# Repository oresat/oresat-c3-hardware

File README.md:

# oresat-c3
## General information
This is the C3 (Command, Communication, and Control) card for OreSat. It acts as the central control point for the entire OreSat project, provides
telemetry to the ground, and receiver commands. It's the "on board computer" (OBC) of the OreSat bus. It has:

- Octavo OSD335x-SM SIP AM335X-based Cortex A8 Microporcessor
- On Semi AX5043-based L Band (1.265 GHz) receiver
- On Semi AX5043-based UHF Band (436.5 MHz) receiver and transmitter with 1W PA.
- Custom radiation tolerant watchdog timer based on the TI TLV1042 comparator.
- 16 GB eMMC flash data storage
- 1 Mbit of FRAM for high reliability state and variable storage
- Supercapacitor-backed up RTC
- Two antenna deployment circuits
- OreSat Power Domain (OPD) control circuitry

Design materials are on Google docs; we'll post links / PDFs soon.

Bill of Materials (BOM) can be found [here](https://docs.google.com/spreadsheets/d/11vG1kWyrAjmbF5QJM-EhXmvQoF6O47japwYlHF802do/edit#gid=1239769296).

## OreSat C3 version 6 (KiCAD)

Fixes for the radio receivers, version 2 backplane pinout, and lots of little tweaks
after our lessons learned on OreSat0. OH, and a COMPLETE REFACTOR since we switched from
the STM32F439 to an Octavo OSD335x-SM and switched from EAGLE to KICAD. Yikes.

### V6 Software

The C3 runs Python code that interacts with the radios, peripherals, and CAN bus. [Here's more information](https://github.com/oresat/oresat-c3-software).

## OreSat C3 version 5 (EAGLE)

C3 V5 flew on Oresat0, Oregon's first satellite! Everything worked great, except for the
radio receivers (L band LNA oscillated, and UHF LNA was turned off in firmware).

### v5 Firmware

The firmware for the C3 card is written in C and runs on top of ChibiOS, a small RTOS.
It is integrated into the [oresat-firmware](https://github.com/oresat/oresat-firmware) repository.
The firmware application for this project is located
[here](https://github.com/oresat/oresat-firmware/tree/c3_capstone/src/f4/app_c3_v1).

## OreSat C3 version 4 (EAGLE)

C3 V4 is our latest version of the C3 card; it's getting ready for flight in 
Q2 2021 in OreSat0. It's got all of the functionality necessary for flight.

## OreSat C3 V3 (2019-2020 ECE Capstone)

The 2018-2019 ECE Capstone brought the card to version 3. It implements an
STM32F446VET6 IC, the full L band receiver with ultistage LNA, and a UHF radio 
with LNA but no PA for transmitting.

## Breadboard Prototype

Most embedded project starts out as a bunch of development boards strung together;
the C3 is no different! The breadboard prototype for the C3 card implements an
STM32F446RE development board connected to two SPI radios, the OreSat
FlatSat backplane via a CAN transceiver and I2C for the OPD interface,
and a SDIO and SPI connected SD/MMC Card. The breadboard implements
stronger pullups for the I2C lines than the GPIO of the STM32 can
provide. It is currently capable of interfacing with and activating the
OPD connected boards.

## License

All materials in this repo are copyright Portland State Aerospace Society and are licensed under the CERN Open Hardware Licence Version 2 -
Strongly Reciprocal (CERN-OHL-S v2), or any later version. A copy of the license is located in [here](LICENSE.md).

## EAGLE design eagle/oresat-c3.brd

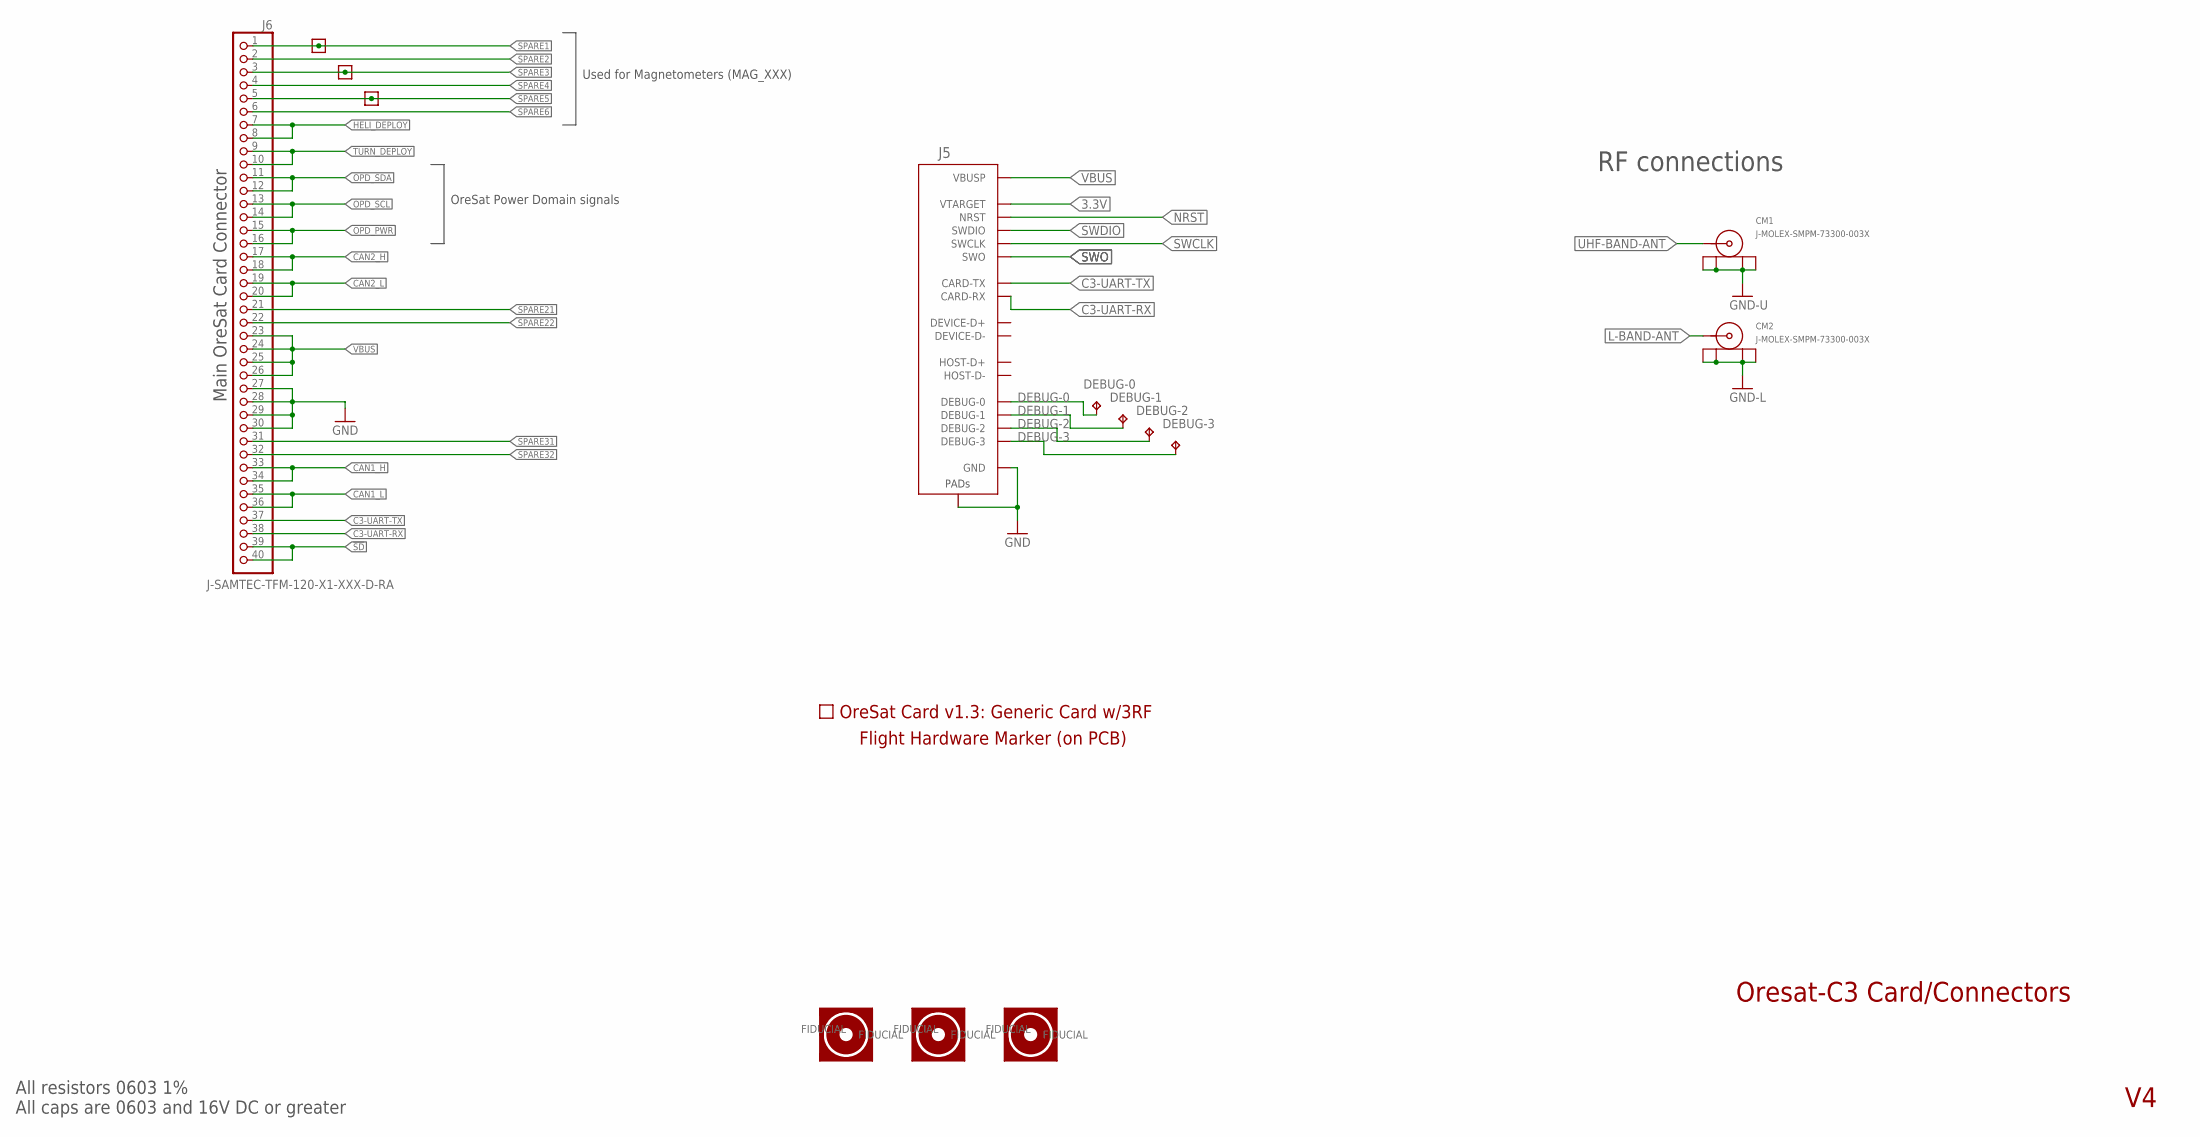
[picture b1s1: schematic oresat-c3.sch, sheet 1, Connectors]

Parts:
CM1, CM2: J-MOLEX-SMPM-73300-003X; J-MOLEX-SMPM-073300-003X; MPN 73300-0020
DEBUG-0, DEBUG-1, DEBUG-2, DEBUG-3: TEST-POINT-SMALL
FIDUCIAL1, FIDUCIAL2, FIDUCIAL3: FIDUCIAL-1.0X2.0
J5: ORESAT-DEBUG-CONNECTOR-ALL; TE_2-1734592-0; MANUFACTURER_PART_NUMBER 2-1734592-0; DIGI-KEY_PART_NUMBER A100287CT-ND
J6: J-SAMTEC-TFM-120-X1-XXX-D-RA; MANUFACTURER_PART_NUMBER TFM-120-01-L-D-RA; DIGI-KEY_PART_NUMBER SAM10145-ND
PCB1: ORESAT-CARD-V1.3-GENERIC-3RF
SPARE3, SPARE4, SPARE5: TEST-POINT-LARGE-SQUARE; 1X01
U$1: FLIGHMARKERNEW; FLIGHTMARKER_NEW_BOARDS

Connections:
3.3V: J5.11 (VTARGET); also elsewhere on the board
!SD: J6.39, J6.40; also elsewhere on the board
C3-UART-RX: J5.12 (CARD-RX), J6.38; also elsewhere on the board
C3-UART-TX: J5.13 (CARD-TX), J6.37; also elsewhere on the board
CAN1_H: J6.33, J6.34; also elsewhere on the board
CAN1_L: J6.35, J6.36; also elsewhere on the board
CAN2_H: J6.17, J6.18; also elsewhere on the board
CAN2_L: J6.19, J6.20; also elsewhere on the board
DEBUG-0: DEBUG-0.TP, J5.17 (DEBUG-0)
DEBUG-1: DEBUG-1.TP, J5.18 (DEBUG-1)
DEBUG-2: DEBUG-2.TP, J5.19 (DEBUG-2)
DEBUG-3: DEBUG-3.TP, J5.20 (DEBUG-3)
GND: J5.3 (GND), J5.6 (GND), J5.9 (GND), J5.PAD1 (PAD), J5.PAD2 (PAD), J6.27, J6.28, J6.29, J6.30; also elsewhere on the board
GND-L: CM2.P$1 (SHIELD3), CM2.P$2 (SHIELD2), CM2.P$3 (SHIELD1), CM2.P$4 (SHIELD); also elsewhere on the board
GND-U: CM1.P$1 (SHIELD3), CM1.P$2 (SHIELD2), CM1.P$3 (SHIELD1), CM1.P$4 (SHIELD); also elsewhere on the board
HELI_DEPLOY: J6.7, J6.8; also elsewhere on the board
L-BAND-ANT: CM2.RF (CENTER); also elsewhere on the board
NRST: J5.10 (NRST); also elsewhere on the board
OPD_PWR: J6.15, J6.16; also elsewhere on the board
OPD_SCL: J6.13, J6.14; also elsewhere on the board
OPD_SDA: J6.11, J6.12; also elsewhere on the board
SPARE1: J6.1, SPARE5.1
SPARE2: J6.2
SPARE3: J6.3, SPARE4.1
SPARE4: J6.4
SPARE5: J6.5, SPARE3.1
SPARE6: J6.6
SPARE21: J6.21
SPARE22: J6.22
SPARE31: J6.31
SPARE32: J6.32
SWCLK: J5.15 (SWCLK); also elsewhere on the board
SWDIO: J5.14 (SWDIO); also elsewhere on the board
SWO: J5.16 (SWO); also elsewhere on the board
TURN_DEPLOY: J6.9, J6.10; also elsewhere on the board
UHF-BAND-ANT: CM1.RF (CENTER); also elsewhere on the board
VBUS: J5.1 (VBUSP), J5.2 (VBUSP), J6.23, J6.24, J6.25, J6.26; also elsewhere on the board

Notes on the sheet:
Oresat-C3 Card/Connectors
Main OreSat Card Connector
RF connections
OreSat Power Domain signals
All resistors 0603 1% All caps are 0603 and 16V DC or greater
Used for Magnetometers (MAG_XXX)

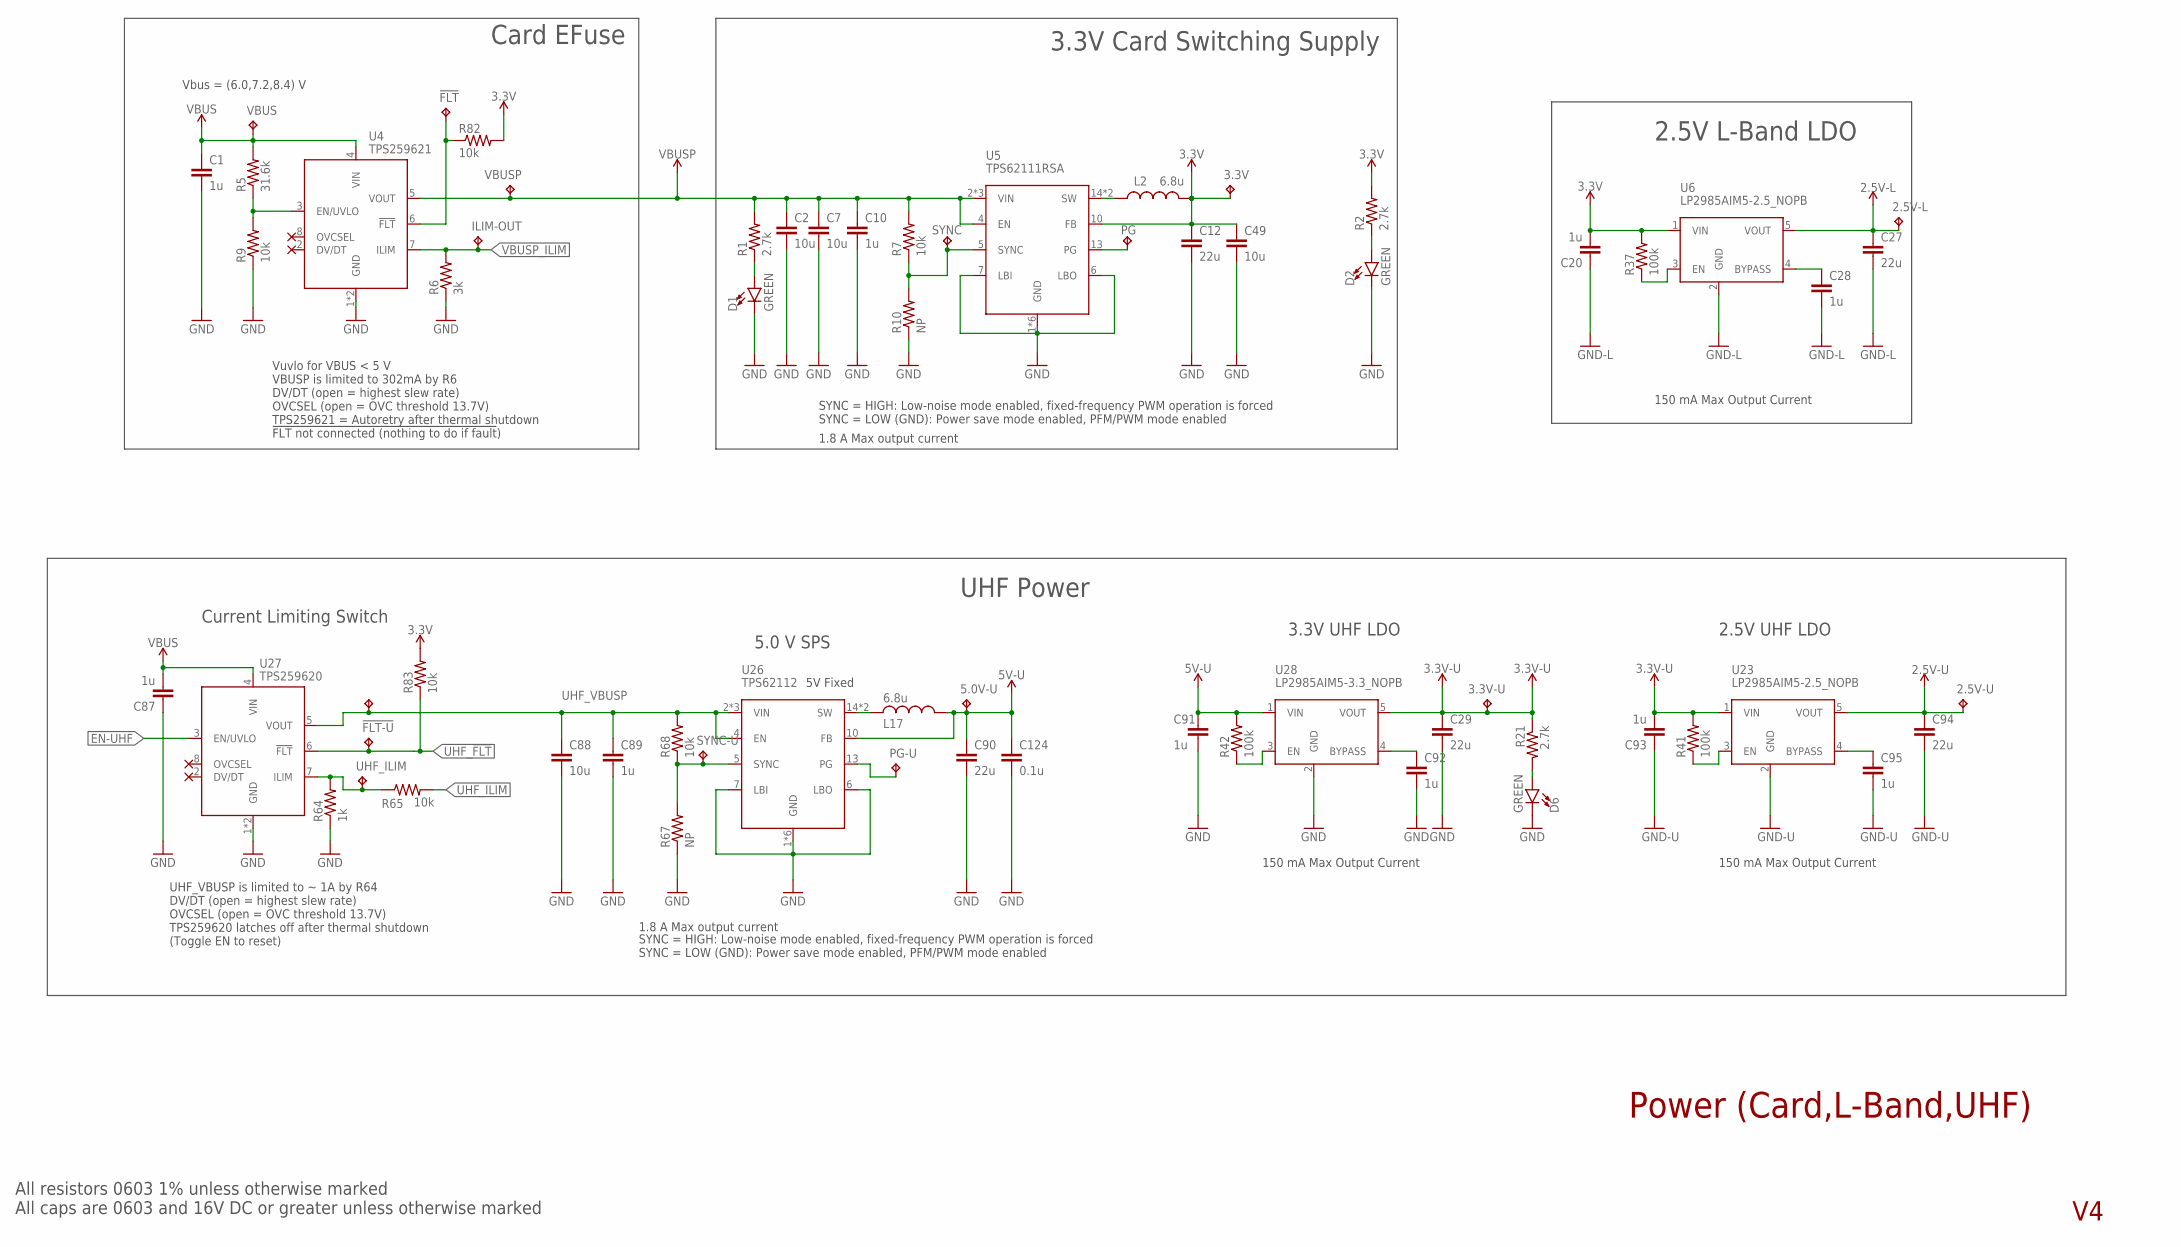
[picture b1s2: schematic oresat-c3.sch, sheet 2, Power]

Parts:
2.5V-L, 2.5V-U, 3.3V, 3.3V-U, 5.0V-U: TEST-POINT-LARGE; 1X01
!FLT: TEST-POINT-LARGE; 1X01
!FLT-U: TEST-POINT-LARGE; 1X01
C1, C10, C20, C28, C87, C89, C91, C92, C93, C95: 1u; .0603-C-NOSILK
C2, C7, C49, C88: 10u; .0603-C-NOSILK
C12, C27, C29, C90, C94: 22u; .0603-C-NOSILK
C124: 0.1u; .0603-C-NOSILK
D1, D2, D6: GREEN; LED-0603; MANUFACTURER_PART_NUMBER 150060VS55040; DIGI-KEY_PART_NUMBER 732-12017-1-ND
ILIM-OUT: TEST-POINT-LARGE; 1X01
L2, L17: 6.8u; ECS-MPI4040; MANUFACTURER_PART_NUMBER ECS-MPI4040R4-6R8-R; DIGI-KEY_PART_NUMBER XC2337CT-ND
PG: TEST-POINT-LARGE; 1X01
PG-U: TEST-POINT-LARGE; 1X01
R1, R2, R21: 2.7k; .0603-C-NOSILK
R5: 31.6k; .0603-C-NOSILK
R6: 3k; .0603-C-NOSILK
R7, R9, R65, R68, R82, R83: 10k; .0603-C-NOSILK
R10, R67: NP; .0603-C-NOSILK
R37, R41, R42: 100k; .0603-C-NOSILK
R64: 1k; .0603-C-NOSILK
SYNC: TEST-POINT-LARGE; 1X01
SYNC-U: TEST-POINT-LARGE; 1X01
TP13, TP19, TP21, TP22: NO-CONNECTNO-CONNECT-DEVICE; NO-CONNECT-FOOTPRINT
U4: TPS259621; SO-POWERPAD-8; MANUFACTURER_PART_NUMBER TPS259621DDAT; DIGI-KEY_PART_NUMBER 296-TPS259621DDATCT-ND
U5: TPS62111RSA; S-PVQFN-16; MANUFACTURER_PART_NUMBER TPS62111RSAT; DIGI-KEY_PART_NUMBER 296-20670-1-ND
U6, U23: LP2985AIM5-2.5_NOPB; SOT-23
U26: TPS62112; S-PVQFN-16; MANUFACTURER_PART_NUMBER TPS62112RSAT; DIGI-KEY_PART_NUMBER 296-19717-1-ND
U27: TPS259620; SO-POWERPAD-8; MANUFACTURER_PART_NUMBER TPS259620DDAT; DIGI-KEY_PART_NUMBER 296-TPS259620DDATCT-ND
U28: LP2985AIM5-3.3_NOPB; SOT-23
UHF_ILIM: TEST-POINT-LARGE; 1X01
VBUS: TEST-POINT-LARGE; 1X01
VBUSP: TEST-POINT-LARGE; 1X01
VBUSP-OUT-U: TEST-POINT-LARGE; 1X01

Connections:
2.5V-L: 2.5V-L.1, C27.1, U6.5 (VOUT); also elsewhere on the board
2.5V-U: 2.5V-U.1, C94.1, U23.5 (VOUT); also elsewhere on the board
3.3V: 3.3V.1, C12.1, C20.2, C49.1, L2.2, R2.2, R37.2, R82.2, R83.2, U5.10 (FB), U6.1 (VIN); also elsewhere on the board
3.3V-U: 3.3V-U.1, C29.1, C93.2, R21.1, R41.2, U23.1 (VIN), U28.5 (VOUT); also elsewhere on the board
5V-U: 5.0V-U.1, C90.1, C91.1, C124.1, L17.1, R42.2, U26.10 (FB), U28.1 (VIN); also elsewhere on the board
!CB_FLT: !FLT.1, R82.1, U4.6 (!FLT)
EN-UHF: U27.3 (EN/UVLO); also elsewhere on the board
EN/UVLO: R5.1, R9.2, U4.3 (EN/UVLO)
GND: C1.2, C2.2, C7.2, C10.2, C12.2, C29.2, C49.2, C87.1, C88.2, C89.2, C90.2, C91.2, C92.2, C124.2, D1.C, D2.C, D6.C, R6.1, R9.1, R10.1, R64.1, R67.1, U4.1 (GND), U4.THERMAL (GND), U5.1 (GND), U5.6 (LBO), U5.7 (LBI), U5.9 (GND), U5.11 (GND), U5.12 (GND), U5.16 (GND), U5.PAD (GND), U26.1 (GND), U26.6 (LBO), U26.7 (LBI), U26.9 (GND), U26.11 (GND), U26.12 (GND), U26.16 (GND), U26.PAD (GND), U27.1 (GND), U27.THERMAL (GND), U28.2 (GND); also elsewhere on the board
GND-L: C20.1, C27.2, C28.2, U6.2 (GND); also elsewhere on the board
GND-U: C93.1, C94.2, C95.2, U23.2 (GND); also elsewhere on the board
LEDPWR3: D6.A, R21.2
unnamed: C95.1, U23.4 (BYPASS)
unnamed: C28.1, U6.4 (BYPASS)
unnamed: R37.1, U6.3 (EN)
unnamed: R41.1, U23.3 (EN)
unnamed: L17.2, U26.14 (SW), U26.15 (SW)
unnamed: PG-U.1, U26.13 (PG)
unnamed: R67.2, R68.1, SYNC-U.1, U26.5 (SYNC)
unnamed: R42.1, U28.3 (EN)
unnamed: C92.1, U28.4 (BYPASS)
unnamed: D1.A, R1.1
unnamed: D2.A, R2.1
SW: L2.1, U5.14 (SW), U5.15 (SW)
TPS62111-PG: PG.1, U5.13 (PG)
TPS62111-SYNC: R7.1, R10.2, SYNC.1, U5.5 (SYNC)
UHF_!FLT: !FLT-U.1, R83.1, U27.6 (!FLT); also elsewhere on the board
UHF_ILIM: R65.2; also elsewhere on the board
UHF_ILIM_RAW: R64.2, R65.1, U27.7 (ILIM), UHF_ILIM.1
UHF_VBUSP: C88.1, C89.1, R68.2, U26.2 (VIN), U26.3 (VIN), U26.4 (EN), U26.8 (VIN), U27.5 (VOUT), VBUSP-OUT-U.1
VBUS: C1.1, C87.2, R5.2, U4.4 (VIN), U27.4 (VIN), VBUS.1; also elsewhere on the board
VBUSP: C2.1, C7.1, C10.1, R1.2, R7.2, U4.5 (VOUT), U5.2 (VIN), U5.3 (VIN), U5.4 (EN), U5.8 (VIN), VBUSP.1
VBUSP_ILIM: ILIM-OUT.1, R6.2, U4.7 (ILIM); also elsewhere on the board

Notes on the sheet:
3.3V Card Switching Supply
Vbus = (6.0,7.2,8.4) V
Card EFuse
All resistors 0603 1% unless otherwise marked All caps are 0603 and 16V DC or greater unless otherwise marked
SYNC = HIGH: Low-noise mode enabled, fixed-frequency PWM operation is forced SYNC = LOW (GND): Power save mode enabled, PFM/PWM mode enabled
5V Fixed
UHF Power
2.5V L-Band LDO
2.5V UHF LDO
3.3V UHF LDO
5.0 V SPS
Current Limiting Switch
UHF_VBUSP is limited to ~ 1A by R64 DV/DT (open = highest slew rate) OVCSEL (open = OVC threshold 13.7V) TPS259620 latches off after thermal shutdown (Toggle EN to reset)
1.8 A Max output current
150 mA Max Output Current
Power (Card,L-Band,UHF)
Vuvlo for VBUS < 5 V VBUSP is limited to 302mA by R6 DV/DT (open = highest slew rate) OVCSEL (open = OVC threshold 13.7V) TPS259621 = Autoretry after thermal shutdown !FLT not connected (nothing to do if fault!)

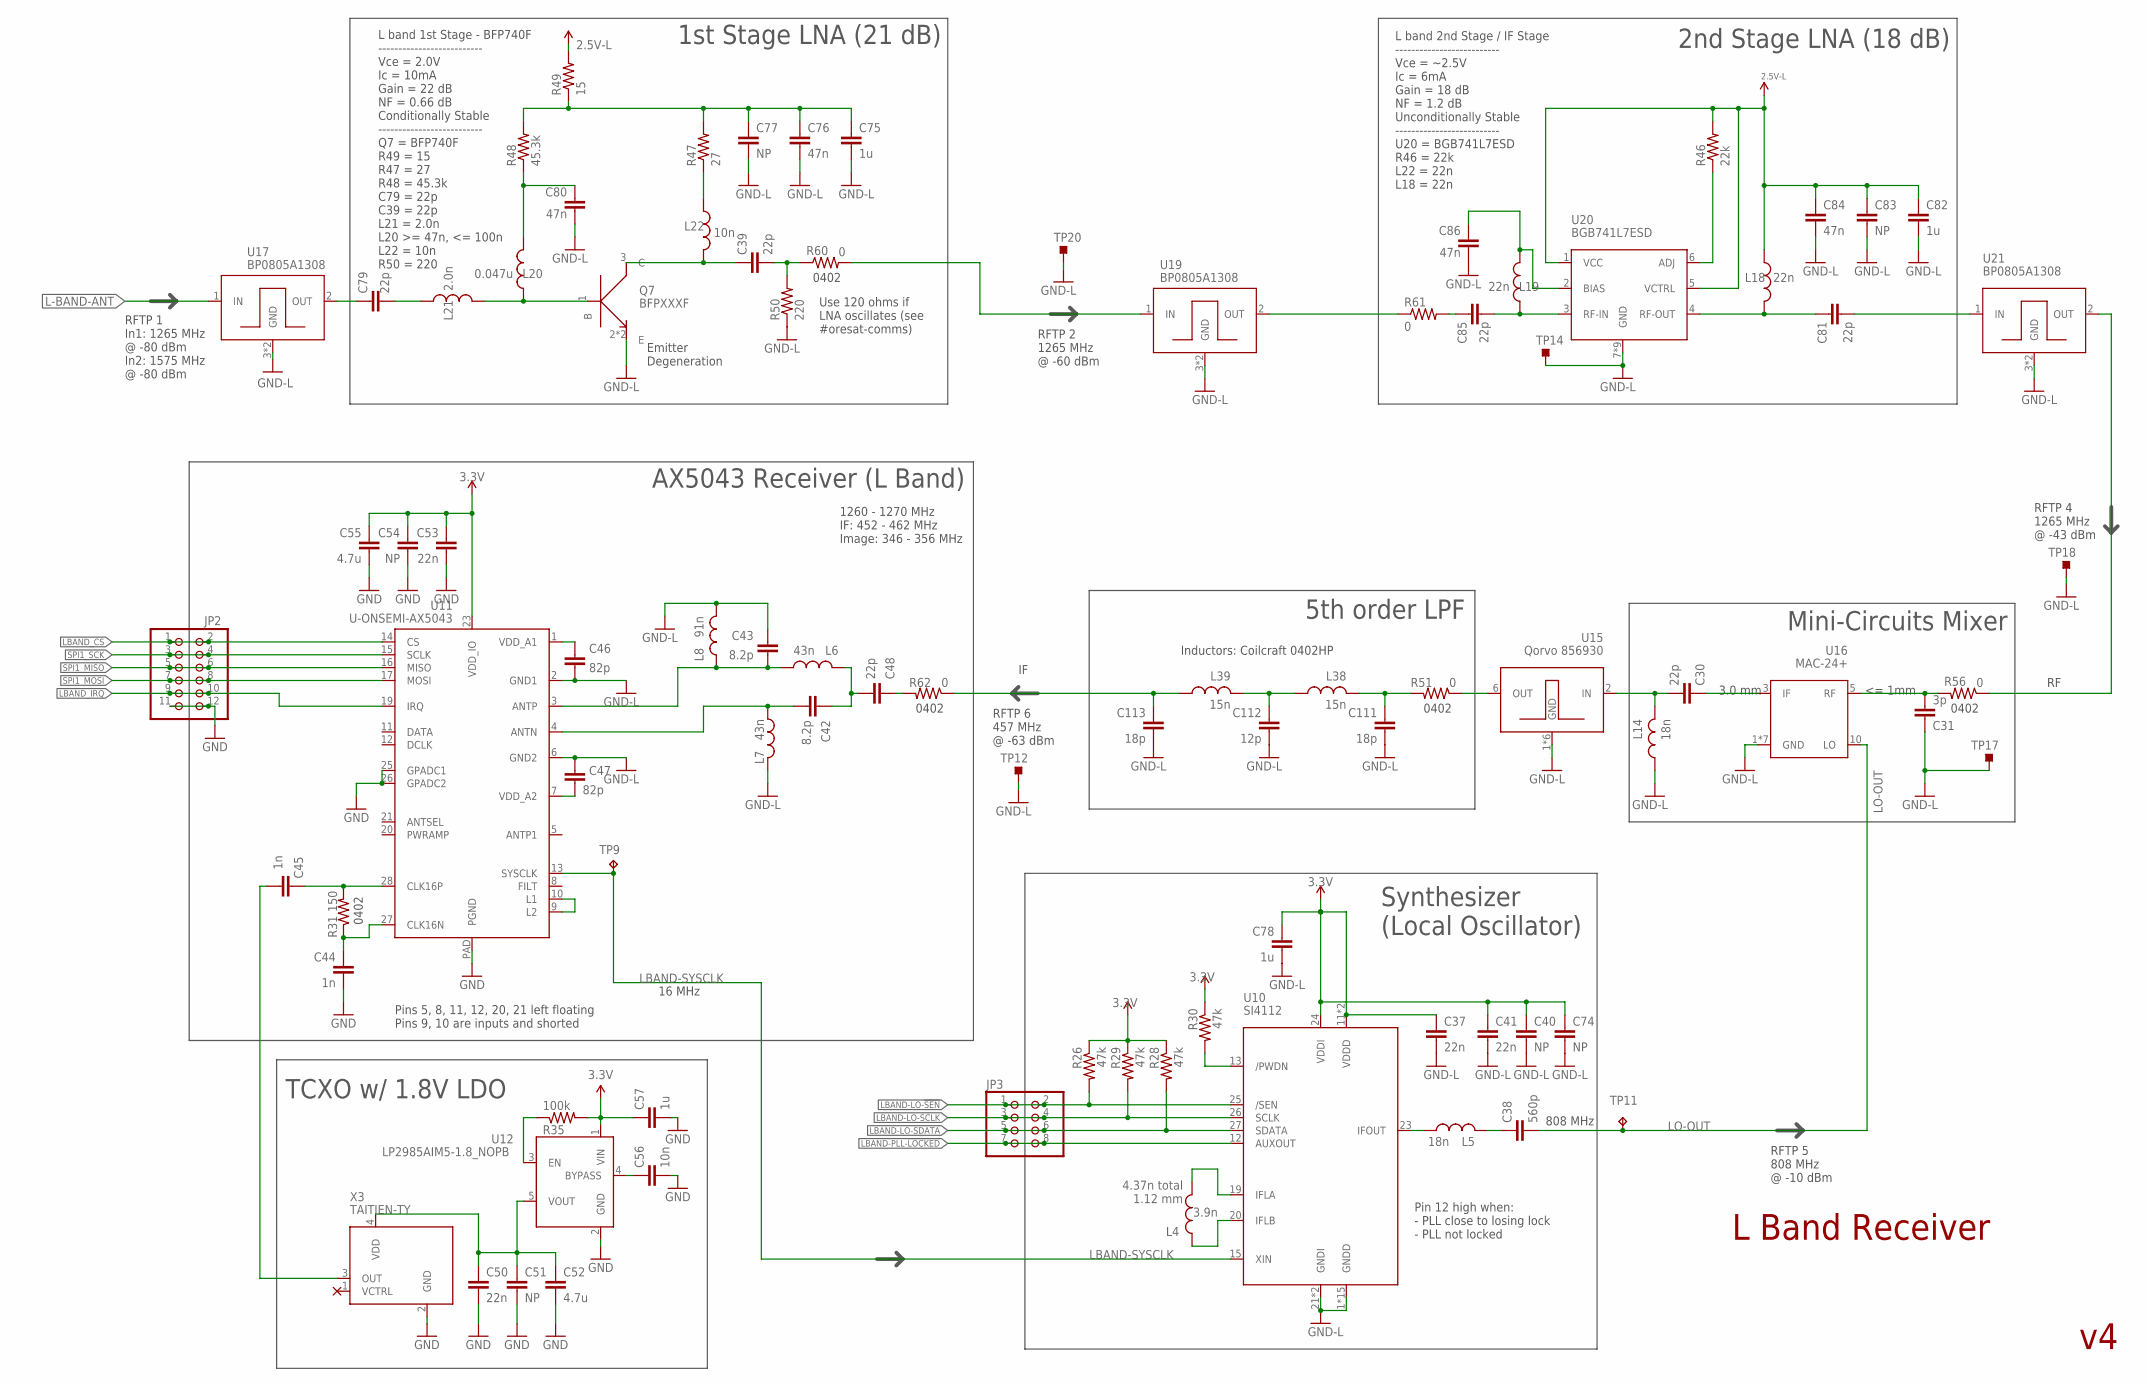
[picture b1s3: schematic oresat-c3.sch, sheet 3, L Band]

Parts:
C30, C39, C48, C79, C81, C85: 22p; .0402-C-NOSILK; MANUFACTURER_PART_NUMBER CL05C220JB5NNNC; DIGI-KEY_PART_NUMBER 1276-1116-1-ND
C31: 3p; .0402-C-NOSILK; MANUFACTURER_PART_NUMBER CL05C030CB5NNNC; DIGI-KEY_PART_NUMBER 1276-1598-1-ND
C37, C41, C50, C53: 22n; .0603-C-NOSILK; MANUFACTURER_PART_NUMBER CL10B223KA8NNNC; DIGI-KEY_PART_NUMBER 1276-1999-1-ND
C38: 560p; .0402-C-NOSILK; MANUFACTURER_PART_NUMBER CL05C561JB5NNNC; DIGI-KEY_PART_NUMBER 1276-1709-1-ND
C40, C51, C54, C74, C77, C83: NP; .0603-C-NOSILK
C42, C43: 8.2p; .0402-C-NOSILK; MANUFACTURER_PART_NUMBER CL05C8R2CB5NNNC; DIGI-KEY_PART_NUMBER 1276-1729-1-ND
C44, C45: 1n; .0402-C-NOSILK; MANUFACTURER_PART_NUMBER CL05C102JB5NNNC; DIGI-KEY_PART_NUMBER 1276-1635-1-ND
C46, C47: 82p; .0402-C-NOSILK; MANUFACTURER_PART_NUMBER CL05C820JB5NNNC; DIGI-KEY_PART_NUMBER 1276-1726-1-ND
C52, C55: 4.7u; .0603-C-NOSILK; MANUFACTURER_PART_NUMBER CL10A475KO8NNNC; DIGI-KEY_PART_NUMBER 1276-1784-1-ND
C56: 10n; .0603-C-NOSILK; MANUFACTURER_PART_NUMBER CL10C103JA8NNNC; DIGI-KEY_PART_NUMBER 1276-2172-1-ND
C57, C75, C78, C82: 1u; .0603-C-NOSILK; MANUFACTURER_PART_NUMBER CC0603KRX5R8BB105; DIGI-KEY_PART_NUMBER 311-1445-1-ND
C76, C80: 47n; .0603-C-NOSILK; MANUFACTURER_PART_NUMBER CL10B473KB8NNNC; DIGI-KEY_PART_NUMBER 1276-1063-1-ND
C84, C86: 47n; .0402-C-NOSILK; MANUFACTURER_PART_NUMBER CL10B473KB8NNNC; DIGI-KEY_PART_NUMBER 1276-1063-1-ND
C111, C113: 18p; .0402-C-NOSILK; MANUFACTURER_PART_NUMBER CL05C180JB5NNNC; DIGI-KEY_PART_NUMBER 1276-1140-1-ND
C112: 12p; .0402-C-NOSILK; MANUFACTURER_PART_NUMBER CL05C120JB5NNNC; DIGI-KEY_PART_NUMBER 1276-1178-1-ND
JP2: PINHD-2X6; 2X06; MANUFACTURER_PART_NUMBER 61301221121; DIGI-KEY_PART_NUMBER 732-5297-ND
JP3: PINHD-2X4; 2X04
L4: 3.9n; .0402-C-NOSILK; MANUFACTURER_PART_NUMBER 0402CS-3N9XGL; MOUSER_PART_NUMBER 994-0402CS-3N9XGLW
L5, L14: 18n; .0402-C-NOSILK; MANUFACTURER_PART_NUMBER 0402HP-18NXGL; DIGI-KEY_PART_NUMBER 2035-1083-1-ND
L6, L7: 43n; .0402-C-NOSILK; MANUFACTURER_PART_NUMBER LQW15AN43NG8ZD; DIGI-KEY_PART_NUMBER 490-15447-1-ND
L8: 91n; .0603-C-NOSILK; MANUFACTURER_PART_NUMBER LQW18AN91NG8ZD; DIGI-KEY_PART_NUMBER 490-15756-1-ND
L18, L19: 22n; .0603-C-NOSILK; MANUFACTURER_PART_NUMBER LQW18AN27NG00D; DIGI-KEY_PART_NUMBER 490-6879-1-ND
L20: 0.047u; .0603-C-NOSILK; MANUFACTURER_PART_NUMBER LQW18AS47NG0ZD; DIGI-KEY_PART_NUMBER 490-15832-1-ND
L21: 2.0n; .0402-C-NOSILK; MANUFACTURER_PART_NUMBER 0402CS-2N0XGL; MOUSER_PART_NUMBER 994-0402CS-2N0XGLW
L22: 10n; .0603-C-NOSILK; MANUFACTURER_PART_NUMBER LQW18AN10NG00D‎; DIGI-KEY_PART_NUMBER 490-6856-1-ND
L38, L39: 15n; .0402-C-NOSILK; MANUFACTURER_PART_NUMBER 0402HP-15NXGLW; DIGI-KEY_PART_NUMBER 2035-1081-1-ND
Q7: BFPXXXF; TSFP4; MANUFACTURER_PART_NUMBER BFP740FH6327XTSA1; DIGI-KEY_PART_NUMBER BFP740FH6327XTSA1CT-ND
R26, R28, R29, R30: 47k; .0603-C-NOSILK; MANUFACTURER_PART_NUMBER RC0603FR-0747KL; DIGI-KEY_PART_NUMBER 311-47.0KHRCT-ND
R31: 150; .0402-C-NOSILK; MANUFACTURER_PART_NUMBER RT0402BRD07150RL; DIGI-KEY_PART_NUMBER YAG4175CT-ND
R35: 100k; .0603-C-NOSILK
R46: 22k; .0603-C-NOSILK; MANUFACTURER_PART_NUMBER ERJ-3EKF2202V; DIGI-KEY_PART_NUMBER P22.0KHCT-ND
R47: 27; .0603-C-NOSILK; MANUFACTURER_PART_NUMBER RMCF0603FT27R0; DIGI-KEY_PART_NUMBER RMCF0603FT27R0CT-ND
R48: 45.3k; .0603-C-NOSILK; MANUFACTURER_PART_NUMBER RMCF0603FT45K3; DIGI-KEY_PART_NUMBER RMCF0603FT45K3CT-ND
R49: 15; .0603-C-NOSILK; MANUFACTURER_PART_NUMBER RMCF0603FT15R0; DIGI-KEY_PART_NUMBER RMCF0603FT15R0CT-ND
R50: 220; .0603-C-NOSILK; MANUFACTURER_PART_NUMBER RMCF0603FT220R; DIGI-KEY_PART_NUMBER RMCF0603FT220RCT-ND
R51, R56, R60, R61, R62: 0; .0402-C-NOSILK; MANUFACTURER_PART_NUMBER RMCF0402ZT0R00; DIGI-KEY_PART_NUMBER RMCF0402ZT0R00CT-ND
TP8: NO-CONNECTNO-CONNECT-DEVICE; NO-CONNECT-FOOTPRINT
TP9, TP11: TEST-PAD-SMD-CIRCLE; TESTPOINT_SMD-CIRCLE-1MM
TP12, TP14, TP17, TP18, TP20: TEST-POINT_SMD-SMD-10SN; TESTPOINT_SMD-10SN
U10: SI4112; QFN28-5X5-WITH-CENTER-PAD; MANUFACTURER_PART_NUMBER SI4112-D-GM; MOUSER_PART_NUMBER 634-SI4112-D-GM
U11: U-ONSEMI-AX5043; QFN28-5X5-WITH-CENTER-PAD; MANUFACTURER_PART_NUMBER AX5043-1-TW30; DIGI-KEY_PART_NUMBER AX5043-1-TW30OSCT-ND
U12: LP2985AIM5-1.8_NOPB; SOT-23; DIGI-KEY_PART_NUMBER LP2985AIM5-1.8/NOPBCT-ND
U15: Qorvo 856930; 3.8X3.8; MANUFACTURER_PART_NUMBER 856930; MOUSER_PART_NUMBER 772-856930
U16: MAC-24+; MANUFACTURER_PART_NUMBER MAC-24+
U17, U19, U21: BP0805A1308; BP0805; MANUFACTURER_PART_NUMBER BP0805A1308ASTR; DIGI-KEY_PART_NUMBER 478-12187-1-ND
U20: BGB741L7ESD; BGB7XXL7ESD; MANUFACTURER_PART_NUMBER BGB741L7ESDE6327XTSA1‎; DIGI-KEY_PART_NUMBER BGB741L7ESDE6327XTSA1CT-ND
X3: TAITIEN-TY; 2.5X2.0; MANUFACTURER_PART_NUMBER TYKTBLSANF-16.000000; DIGI-KEY_PART_NUMBER 1664-1323-1-ND

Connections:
1V8: C50.1, C51.1, C52.1, U12.5 (VOUT), X3.4 (VDD)
2.5V-L: C82.1, C83.1, C84.1, L18.1, R46.2, R49.2, U20.1 (VCC), U20.5 (VCTRL); also elsewhere on the board
3.3V: C37.1, C40.1, C41.1, C53.1, C54.1, C55.1, C57.1, C74.1, C78.1, R26.1, R28.1, R29.1, R30.1, R35.2, U10.11 (VDDD), U10.17 (VDDD), U10.24 (VDDI), U11.23 (VDD_IO), U12.1 (VIN); also elsewhere on the board
ANTN1: C42.2, L7.2, U11.4 (ANTN)
ANTP2: C43.2, L6.2, L8.1, U11.3 (ANTP)
B1: L20.1, L21.2, Q7.1 (B)
C1: C39.1, L22.2, Q7.3 (C)
CAPS1: C75.1, C76.1, C77.1, R47.2, R48.2, R49.1
CLKN1: C44.1, R31.1, U11.27 (CLK16N)
CLKP1: C45.1, R31.2, U11.28 (CLK16P)
GND: C44.2, C50.2, C51.2, C52.2, C53.2, C54.2, C55.2, C56.2, C57.2, JP2.11, JP2.12, U11.25 (GPADC1), U11.26 (GPADC2), U11.PAD (PGND), U12.2 (GND), X3.2 (GND); also elsewhere on the board
GND-L: C31.1, C37.2, C40.2, C41.2, C43.1, C46.2, C47.1, C74.2, C75.2, C76.2, C77.2, C78.2, C80.2, C82.2, C83.2, C84.2, C86.2, C111.2, C112.2, C113.2, L7.1, L8.2, L14.2, Q7.2 (E), Q7.4 (E), R50.1, TP12.TP, TP14.TP, TP17.TP, TP18.TP, TP20.TP, U10.1 (GNDD), U10.2 (GNDD), U10.3 (GNDD), U10.4 (GNDD), U10.5 (GNDD), U10.6 (GNDD), U10.7 (GNDD), U10.8 (GNDD), U10.9 (GNDD), U10.10 (GNDD), U10.14 (GNDD), U10.16 (GNDD), U10.18 (GNDD), U10.21 (GNDI), U10.22 (GNDI), U10.28 (GNDD), U10.PAD (GNDD), U11.2 (GND1), U11.6 (GND2), U15.1 (GND), U15.3 (GND), U15.4 (GND), U15.5 (GND), U15.7 (GND), U15.8 (GND), U16.1 (GND), U16.2 (GND), U16.4 (GND), U16.6 (GND), U16.7 (GND), U16.8 (GND), U16.9 (GND), U17.3 (GND), U17.4 (GND), U19.3 (GND), U19.4 (GND), U20.7 (GND), U20.8 (GND), U20.9 (GND), U20.10 (GND), U20.11 (GND), U20.12 (GND), U20.13 (GND), U20.14 (GND), U20.15 (GND), U21.3 (GND), U21.4 (GND); also elsewhere on the board
IF-SAW-OUT: C111.1, L38.1, R51.2
L-BAND-ANT: U17.1 (IN); also elsewhere on the board
L-BAND-RX: C113.1, L39.2, R62.1
L-BFP-LNA-RF_IN: C79.1, U17.2 (OUT)
L-BFP-LNA-RF_OUT: R60.2, U19.1 (IN)
L-BGB-LNA-RF_IN: R61.1, U19.2 (OUT)
L-BGB-LNA-RF_OUT: C81.2, U21.1 (IN)
LBAND-LO-!SEN: JP3.1, JP3.2, R26.2, U10.25 (/SEN); also elsewhere on the board
LBAND-LO-SCLK: JP3.3, JP3.4, R29.2, U10.26 (SCLK); also elsewhere on the board
LBAND-LO-SDATA: JP3.5, JP3.6, R28.2, U10.27 (SDATA); also elsewhere on the board
LBAND-PLL-!LOCKED: JP3.7, JP3.8, U10.12 (AUXOUT); also elsewhere on the board
LBAND-SYSCLK: TP9.TP, U10.15 (XIN), U11.13 (SYSCLK)
LBAND_CS: JP2.1, JP2.2, U11.14 (CS); also elsewhere on the board
LBAND_IRQ: JP2.9, JP2.10, U11.19 (IRQ); also elsewhere on the board
LO-OUT: C38.2, TP11.TP, U16.10 (LO)
MIX-IF-OUT: C30.2, L14.1, U15.2 (IN)
unnamed: R30.2, U10.13 (/PWDN)
unnamed: C45.2, X3.3 (OUT)
unnamed: U11.9 (L2), U11.10 (L1)
unnamed: C46.1, U11.1 (VDD_A1)
unnamed: C47.2, U11.7 (VDD_A2)
unnamed: C56.1, U12.4 (BYPASS)
unnamed: C42.1, C48.2, L6.1
unnamed: C31.2, R56.2, U16.5 (RF)
unnamed: C30.1, U16.3 (IF)
unnamed: R35.1, U12.3 (EN)
unnamed: C80.1, L20.2, R48.1
unnamed: L22.1, R47.1
unnamed: C79.2, L21.1
unnamed: L4.2, U10.19 (IFLA)
unnamed: L4.1, U10.20 (IFLB)
unnamed: L5.1, U10.23 (IFOUT)
unnamed: C38.1, L5.2
unnamed: C81.1, L18.2, U20.4 (RF-OUT)
unnamed: R46.1, U20.6 (ADJ)
unnamed: C85.2, L19.1, U20.3 (RF-IN)
unnamed: C86.1, L19.2, U20.2 (BIAS)
unnamed: C48.1, R62.2
unnamed: C85.1, R61.2
unnamed: C112.1, L38.2, L39.1
unnamed: C39.2, R50.2, R60.1
unnamed: R51.1, U15.6 (OUT)
unnamed: R56.1, U21.2 (OUT)
SPI1_MISO: JP2.5, JP2.6, U11.16 (MISO); also elsewhere on the board
SPI1_MOSI: JP2.7, JP2.8, U11.17 (MOSI); also elsewhere on the board
SPI1_SCK: JP2.3, JP2.4, U11.15 (SCLK); also elsewhere on the board

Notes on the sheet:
L Band Receiver
1260 - 1270 MHz IF: 452 - 462 MHz Image: 346 - 356 MHz
4.37n total 1.12 mm
808 MHz
Pin 12 high when: - PLL close to losing lock - PLL not locked
3.0 mm
<= 1mm
Pins 5, 8, 11, 12, 20, 21 left floating Pins 9, 10 are inputs and shorted
L band 1st Stage - BFP740F -------------------------- Vce = 2.0V Ic = 10mA Gain = 22 dB NF = 0.66 dB Conditionally Stable -------------------------- Q7 = BFP740F R49 = 15 R47 = 27 R48 = 45.3k C79 = 22p C39 = 22p L21 = 2.0n L20 >= 47n, <= 100n L22 = 10n R50 = 220
Emitter Degeneration
L band 2nd Stage / IF Stage -------------------------- Vce = ~2.5V Ic = 6mA Gain = 18 dB NF = 1.2 dB Unconditionally Stable -------------------------- U20 = BGB741L7ESD R46 = 22k L22 = 22n L18 = 22n
5th order LPF
Mini-Circuits Mixer
2nd Stage LNA (18 dB)
1st Stage LNA (21 dB)
TCXO w/ 1.8V LDO
AX5043 Receiver (L Band)
Synthesizer (Local Oscillator)
Inductors: Coilcraft 0402HP
16 MHz
0402
RFTP 1 In1: 1265 MHz @ -80 dBm In2: 1575 MHz @ -80 dBm
RFTP 2 1265 MHz @ -60 dBm
RFTP 4 1265 MHz @ -43 dBm
RFTP 6 457 MHz @ -63 dBm
RFTP 5 808 MHz @ -10 dBm
Use 120 ohms if LNA oscillates (see #oresat-comms)

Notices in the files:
parts and their libraries:
SparkFun-Connectors: Licensing: Creative Commons ShareAlike 4.0 International - https://creativecommons.org/licenses/by-sa/4.0
SparkFun: Licensing: CC v3.0 Share-Alike You are welcome to use this library for commercial purposes.
